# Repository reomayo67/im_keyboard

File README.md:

# im_keyboard

 33% ergonomic layout Keyboard. Atmega32u4 powered

HAS NOT BEEN ASSEMBLED YET

ALOT of this is heaviliy inspired by ScottoKeebs, I am using his footprint and symbol libraries in kicad, so shoutout to him. He was a huge help in making this possible. [ScottoKeebs](https://github.com/joe-scotto/scottokeebs) Huge inspo from [Plaid](https://github.com/hsgw/plaid)

So I just wanted to make an intro into the hardware engineering space with a simple pcb mkb. This is my first ever officially documented project, so yea. Ive been wanting to make one for a while, and eventually want to evolve into making abuncha wacky ergo keyboards and other stuff like that.

this keyboard uses only through hole components and relies on a devboard. Any type of mx switch can be used, it is not hot swap ready though.

The Case is 3d printed, made with fusion360.

Here are the youtube videos i watched in order to make this

https://www.youtube.com/watch?v=7azQkSu0m_U&t=491s

https://www.youtube.com/watch?v=8WXpGTIbxlQ&t=3s

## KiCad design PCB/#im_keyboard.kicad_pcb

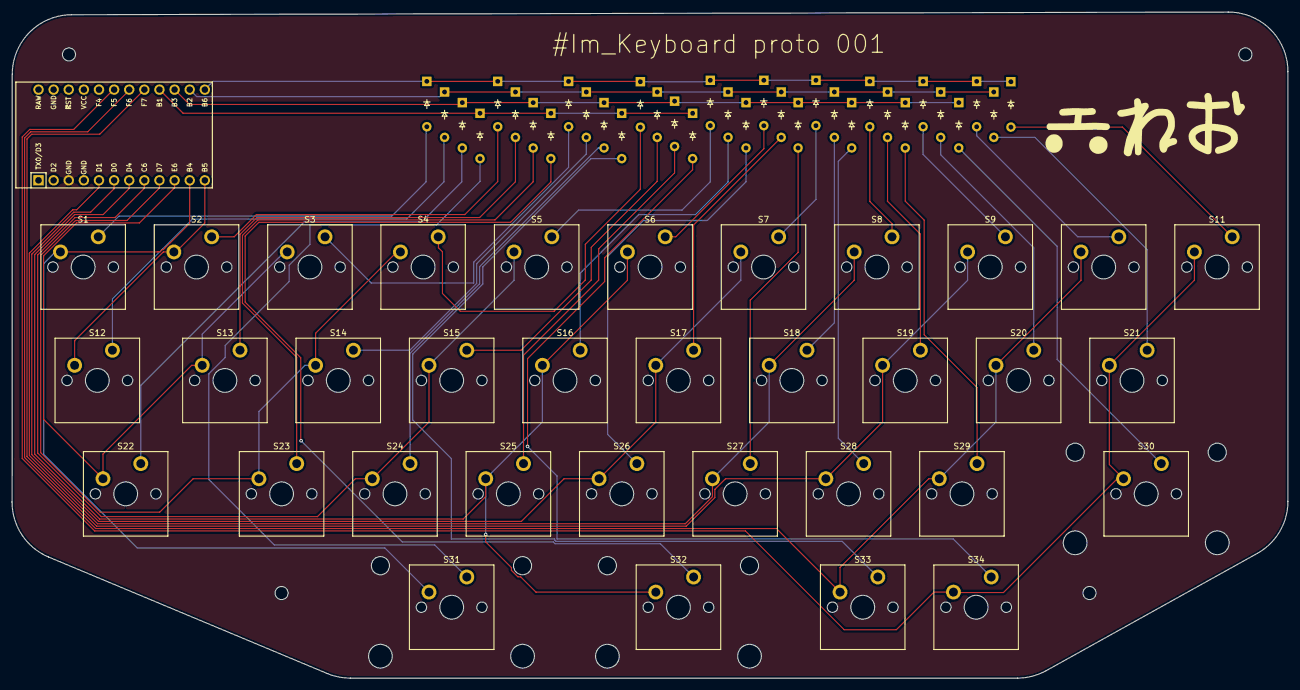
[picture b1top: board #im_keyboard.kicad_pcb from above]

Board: 2 copper layers, 214.3 x 111.9 mm, 73 parts (0 on the bottom side), 49 nets.

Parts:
D1, D2, D3, D4, D5, D6, D7, D8, D9, D10, D11, D12, D13, D14, D15, D16, D17, D18, D19, D20, D21, D22, D23, D24, D25, D26, D27, D28, D29, D30, D31, D32, D33, D34: Diode_DO-35
H1, H2, H3, H4: MountingHole; MountingHole_2.2mm_M2
S1, S2, S3, S4, S5, S6, S7, S8, S9, S10, S11, S12, S13, S14, S15, S16, S17, S18, S19, S20, S21, S22, S23, S24, S25, S26, S27, S28, S29, S30, S31, S32, S33, S34: MX_PCB_1.00u
U1: Arduino_Pro_Micro

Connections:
Col0: S1.1, S31.1, U1.11 (8/PB4)
Col1: S2.1, S12.1, U1.12 (9/PB5)
Col2: S3.1, S13.1, S22.1, U1.10 (7/PE6)
Col3: S4.1, S14.1, S23.1, U1.9 (6/PD7)
Col4: S5.1, S15.1, S24.1, U1.8 (5/PC6)
Col5: S6.1, S16.1, S25.1, S32.1, U1.7 (4/PD4)
Col6: S7.1, S17.1, S26.1, U1.6 (3/PD0)
Col7: S8.1, S18.1, S27.1, U1.5 (2/PD1)
Col8: S9.1, S19.1, S28.1, U1.17 (A0/PF7)
Col9: S10.1, S20.1, S29.1, S33.1, U1.18 (A1/PF6)
Col10: S11.1, S21.1, S30.1, S34.1, U1.19 (A2/PF5)
unnamed: D1.2 (A), S1.2
unnamed: D2.2 (A), S2.2
unnamed: D3.2 (A), S3.2
unnamed: D4.2 (A), S4.2
unnamed: D5.2 (A), S5.2
unnamed: D6.2 (A), S6.2
unnamed: D7.2 (A), S7.2
unnamed: D8.2 (A), S8.2
unnamed: D9.2 (A), S9.2
unnamed: D10.2 (A), S10.2
unnamed: D11.2 (A), S11.2
unnamed: D12.2 (A), S12.2
unnamed: D13.2 (A), S13.2
unnamed: D14.2 (A), S14.2
unnamed: D15.2 (A), S15.2
unnamed: D16.2 (A), S16.2
unnamed: D17.2 (A), S17.2
unnamed: D18.2 (A), S18.2
unnamed: D19.2 (A), S19.2
unnamed: D20.2 (A), S20.2
unnamed: D21.2 (A), S21.2
unnamed: D22.2 (A), S22.2
unnamed: D23.2 (A), S23.2
unnamed: D24.2 (A), S24.2
unnamed: D25.2 (A), S25.2
unnamed: D26.2 (A), S26.2
unnamed: D27.2 (A), S27.2
unnamed: D28.2 (A), S28.2
unnamed: D29.2 (A), S29.2
unnamed: D30.2 (A), S30.2
unnamed: D31.2 (A), S31.2
unnamed: D32.2 (A), S32.2
unnamed: D33.2 (A), S33.2
unnamed: D34.2 (A), S34.2
Row0: D1.1 (K), D2.1 (K), D3.1 (K), D4.1 (K), D5.1 (K), D6.1 (K), D7.1 (K), D8.1 (K), D9.1 (K), D10.1 (K), D11.1 (K), U1.13 (10/PB6)
Row1: D12.1 (K), D13.1 (K), D14.1 (K), D15.1 (K), D16.1 (K), D17.1 (K), D18.1 (K), D19.1 (K), D20.1 (K), D21.1 (K), U1.14 (16/PB2)
Row2: D22.1 (K), D23.1 (K), D24.1 (K), D25.1 (K), D26.1 (K), D27.1 (K), D28.1 (K), D29.1 (K), D30.1 (K), U1.15 (14/PB3)
Row3: D31.1 (K), D32.1 (K), D33.1 (K), D34.1 (K), U1.16 (15/PB1)

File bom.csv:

Designator,Footprint,Quantity,Value,LCSC Part #
"D1, D10, D11, D12, D13, D14, D15, D16, D17, D18, D19, D2, D20, D21, D22, D23, D24, D25, D26, D27, D28, D29, D3, D30, D31, D32, D33, D34, D4, D5, D6, D7, D8, D9",Diode_DO-35,34,~,
"S1, S10, S11, S12, S13, S14, S15, S16, S17, S18, S19, S2, S20, S21, S22, S23, S24, S25, S26, S27, S28, S29, S3, S30, S31, S32, S33, S34, S4, S5, S6, S7, S8, S9",MX_PCB_1.00u,34,~,
U1,Arduino_Pro_Micro,1,Arduino_Pro_Micro,
